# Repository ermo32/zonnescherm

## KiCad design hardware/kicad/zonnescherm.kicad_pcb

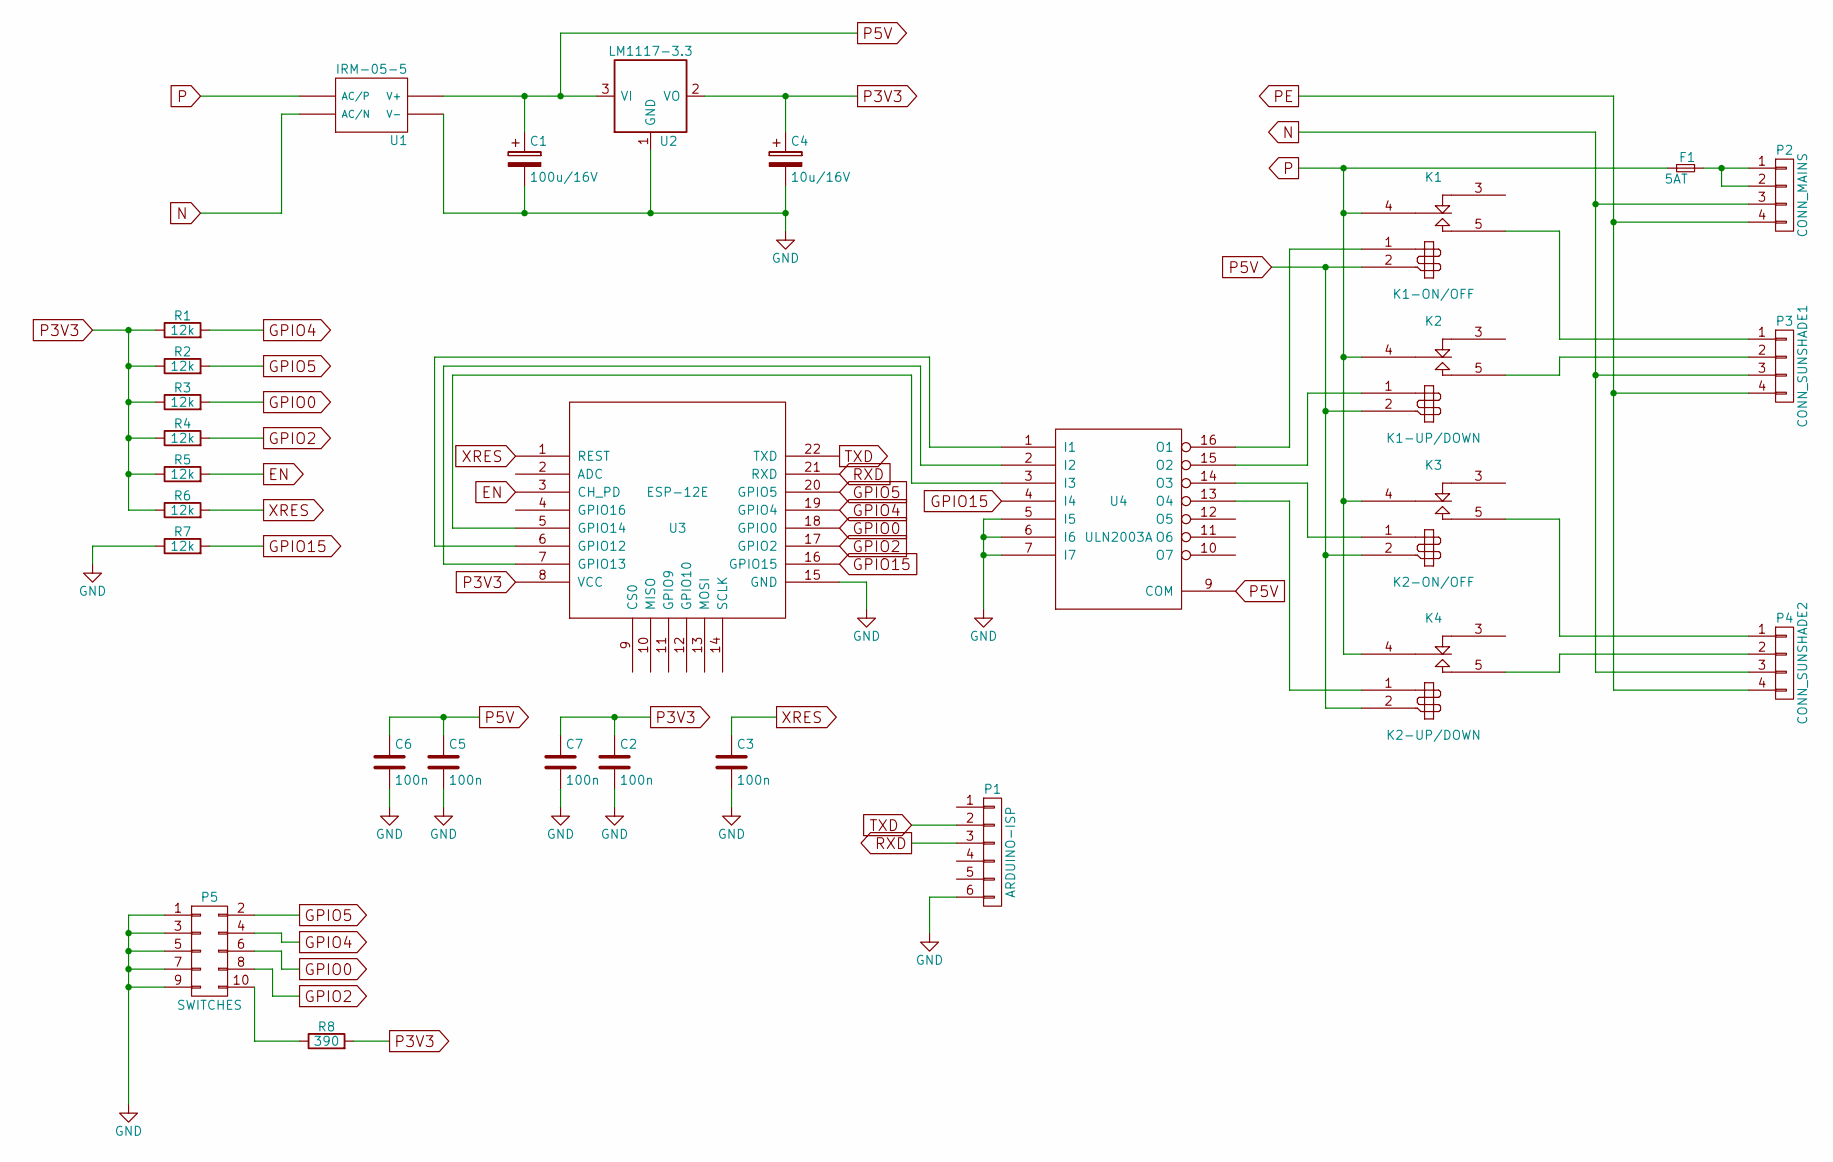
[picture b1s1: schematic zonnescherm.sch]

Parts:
C1: 100u/16V; c_elec_8x6.5
C2, C3, C5, C6, C7: 100n; C_0805_HandSoldering
C4: 10u/16V; c_elec_4x5.8
F1: 5AT; Fuseholder5x20_horiz_SemiClosed_Casing10x25mm
K1: K1-ON/OFF; FTR_LY
K2: K1-UP/DOWN; FTR_LY
K3: K2-ON/OFF; FTR_LY
K4: K2-UP/DOWN; FTR_LY
P1: ARDUINO-ISP; Pin_Header_Straight_1x06
P2: CONN_MAINS; AKL-330-4
P3: CONN_SUNSHADE1; AKL-330-4
P4: CONN_SUNSHADE2; AKL-330-4
P5: SWITCHES; Pin_Header_Straight_2x05
R1, R2, R3, R4, R5, R6, R7: 12k; R_0805_HandSoldering
R8: 390; R_0805_HandSoldering
U1: IRM-05-5; IRM-05
U2: LM1117-3.3; TO-263-3Lead
U3: ESP-12E
U4: ULN2003A; SO-16-N

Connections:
EN: R5.2, U3.3 (CH_PD)
GND: C1.2, C2.2, C3.2, C4.2, C5.2, C6.2, C7.2, P1.6, P5.1, P5.3, P5.5, P5.7, P5.9, R7.1, U1.4 (V-), U2.1 (GND), U3.15 (GND), U4.5 (I5), U4.6 (I6), U4.7 (I7), U4.8 (GND)
GPIO0: P5.6, R3.2, U3.18 (GPIO0)
GPIO2: P5.8, R4.2, U3.17 (GPIO2)
GPIO4: P5.4, R1.2, U3.19 (GPIO4)
GPIO5: P5.2, R2.2, U3.20 (GPIO5)
GPIO15: R7.2, U3.16 (GPIO15), U4.4 (I4)
N: P2.3, P3.3, P4.3, U1.2 (AC/N)
unnamed: F1.2, P2.1, P2.2
unnamed: K1.1 (8), U4.16 (O1)
unnamed: K1.5 (T1), P3.1
unnamed: K2.1 (8), U4.15 (O2)
unnamed: K2.5 (T1), P3.2
unnamed: K3.1 (8), U4.14 (O3)
unnamed: K3.5 (T1), P4.1
unnamed: K4.1 (8), U4.13 (O4)
unnamed: K4.5 (T1), P4.2
unnamed: P5.10, R8.1
unnamed: U3.5 (GPIO14), U4.3 (I3)
unnamed: U3.6 (GPIO12), U4.1 (I1)
unnamed: U3.7 (GPIO13), U4.2 (I2)
P: F1.1, K1.4 (C1), K2.4 (C1), K3.4 (C1), K4.4 (C1), U1.1 (AC/P)
P3V3: C2.1, C4.1, C7.1, R1.1, R2.1, R3.1, R4.1, R5.1, R6.1, R8.2, U2.2 (VO), U2.4 (VO), U3.8 (VCC)
P5V: C1.1, C5.1, C6.1, K1.2 (9), K2.2 (9), K3.2 (9), K4.2 (9), U1.3 (V+), U2.3 (VI), U4.9 (COM)
PE: P2.4, P3.4, P4.4
RXD: P1.3, U3.21 (RXD)
TXD: P1.2, U3.22 (TXD)
XRES: C3.1, R6.2, U3.1 (REST)

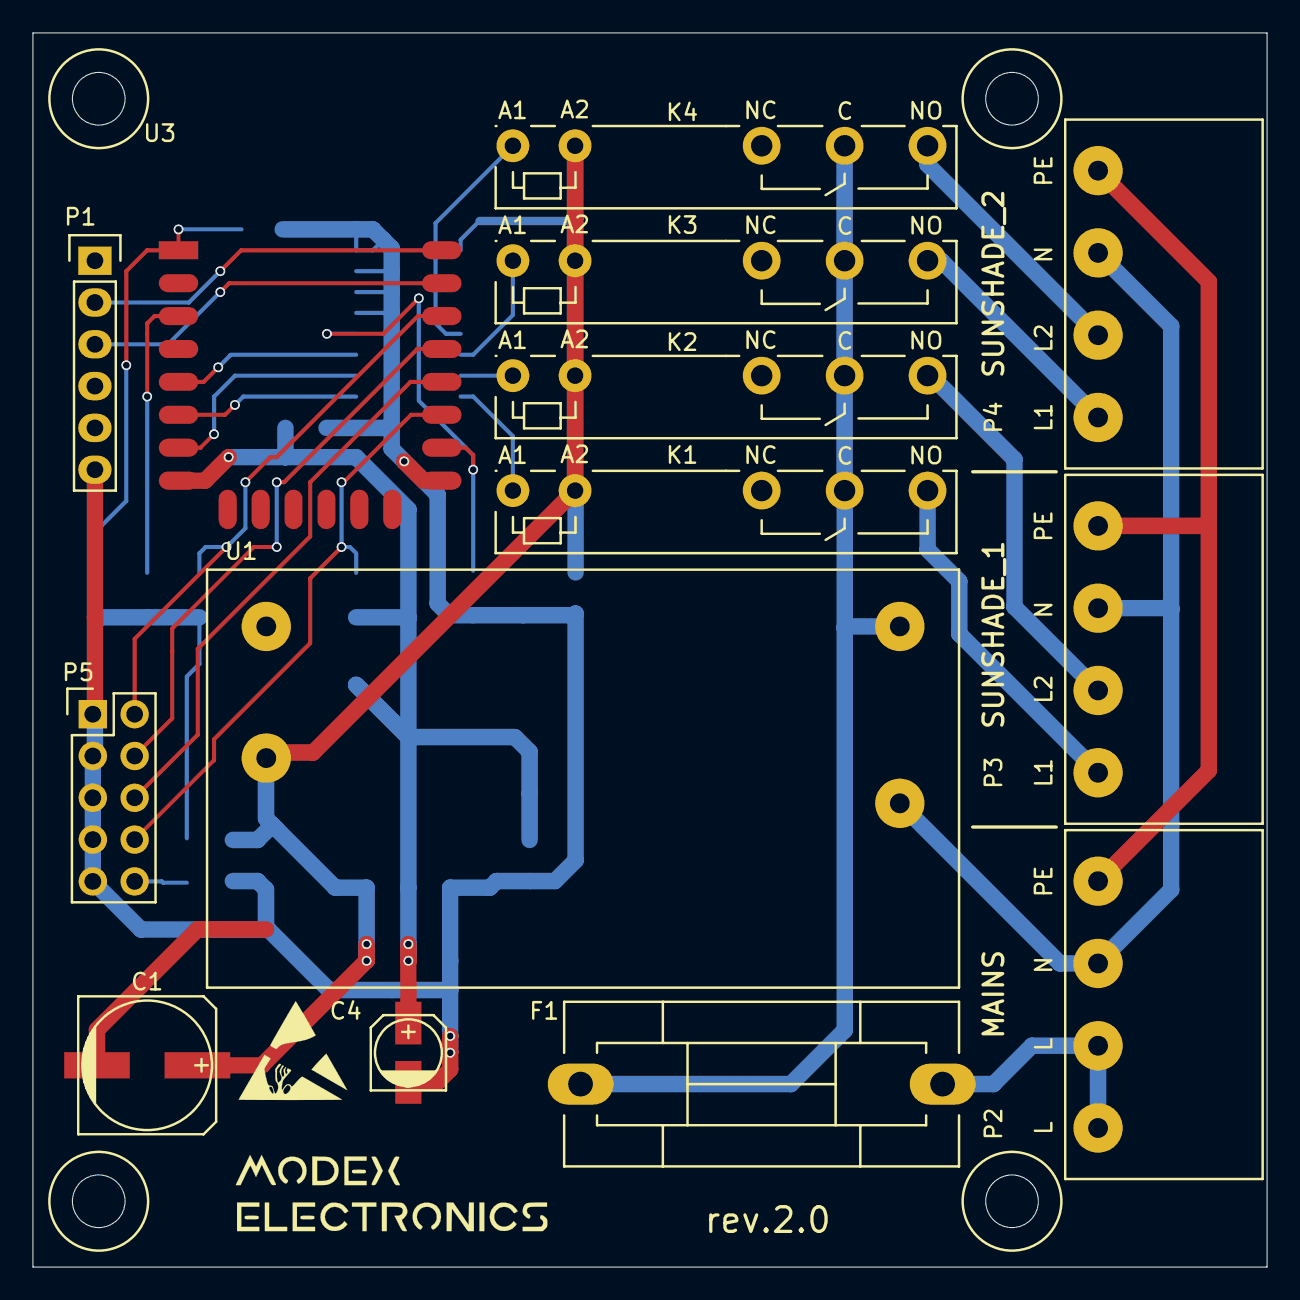
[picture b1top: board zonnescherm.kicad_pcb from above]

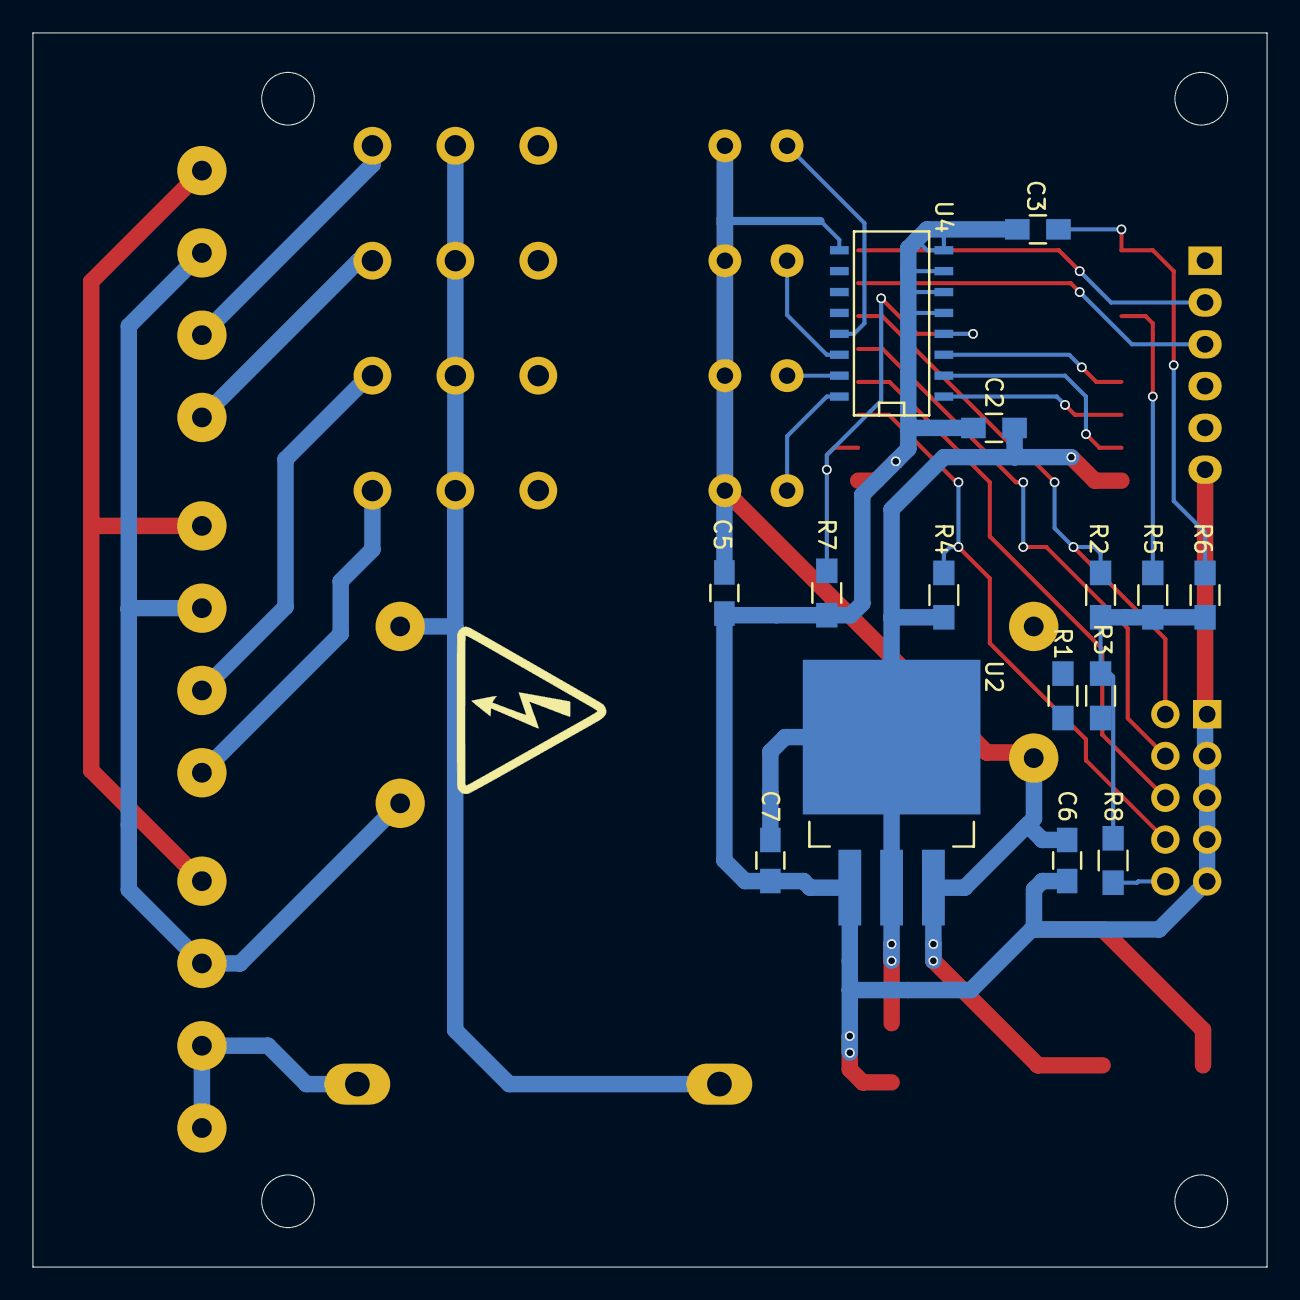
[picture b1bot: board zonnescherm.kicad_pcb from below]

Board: 2 copper layers, 75.0 x 75.0 mm, 29 parts (15 on the bottom side), 28 nets.

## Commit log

2016-07-12 Added Kicad project
2016-07-12 Kicad and ESP8266 libraries added
2016-07-12 Added ESP-12
2016-07-12 Added Android project
2016-07-12 Added documentation and Modex library
2016-07-12 Added file
2016-07-12 Added test project for Android
2016-07-12 Deleted file
2016-07-12 Added library symbols
2016-07-12 Added Python buienradar script
2016-07-14 Added IPC guidlines for PCB design
2016-07-14 Updated schematic
2016-07-15 Added footprint library modex
2016-07-15 Removed modex.pretty library
2016-07-15 Added modex.pretty footprint library
2016-07-15 Removed footprint from modex.pretty library
2016-07-15 Added new footprint
2016-07-15 Updated design
2016-07-15 Added footprints
2016-07-17 Added AKL-330-4 footprint
2016-07-17 Updated layout
2016-07-20 Updated PCB layout
2016-07-21 Updated PCB
2016-07-24 Added logo
2016-07-27 Updated layout, added text etc.
2016-07-30 Added high voltage logo
2016-07-31 Added ESD logo and generated gerberfiles and drill files. Send design tot PCBWAY.com
2016-07-31 Added invoice PCBWay
2016-08-07 V2 is de verbeterde versie zonder delay functie
2016-09-04 Added Python script to control the sunshade by a Raspberry Pi. This version first checks the status of the sunshades before sending the commands.
2016-09-07 Updated the footprint and schematic symbol of the AC/DC converter module
2016-09-07 Added datasheets of enclosure, switch and connector block.
2016-09-07 Updated layout with new footprint.
2016-09-10 Changed layout of the PCB.
2016-09-11 Added picture of the assembled PCB. Changed PCB for release 2.0. Not ready yet.
2016-09-14 Added gitignore file.
2016-09-14 Cleanup design.
2016-09-14 Added gitignore file in the KiCad directory.
2016-09-15 Added system overview document.
2016-09-15 Updated system overview.
2016-09-17 Changed output configuration to enable global usage of the project.
2016-09-25 Updated libraries.
2016-09-25 Added KiCAD libraries.
2016-09-25 Deleted libraries.
2018-01-21 Added new version wit WiFiMananger.
2018-01-21 Cleaned code.
2018-05-29 Added pictures.
2018-06-10 Added new revision of buienradar application.
